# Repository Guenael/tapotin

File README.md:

# tapotin

# Description

Tapotin is a simple 42-keys ortho-linear keyboard, based on QMK driver and a Raspberry Pico (RP2040). The design is heavily inspired by the community, specially by [Pi5Keyboard](https://github.com/luke-schutt/Pi5Keyboard) and [chocV](https://github.com/brickbots/chocV) projects.

Kicad was used for the PCB design, and it was a nice project to switch from professional tools to a community/free PCB editor. For this first version, I used a RPi Pico board, but I plan to solder the RP2040 directly on the main PCB if I like this new keyboard.

# My requirements

- [QMK](https://qmk.fm/) based
- [RP2040](https://en.wikipedia.org/wiki/RP2040) based
- Mono-block (non-split keyboard, I tried it, and I don't like it)
- [Ortholinear](https://en.wiktionary.org/wiki/ortholinear) (offset only for the pinky)
- Left/right clear separation
- Angle 2x 10°
- 42 keys: 2*((3*6)+3)
- [Miryoku](https://github.com/manna-harbour/miryoku) layout based
- PCB specs:
  - Base/solder : 1.6mm
  - Keys plate  : 1.2mm

# Assembly

The RPi Pico board is soldered up-side down, and touch both PCB (main & key plate)

PCB layers overviews:

Back of the keyboard:

# My layout 

Here there be dragons... 20 years ago, I designed my own version of a [Dvorak layout](https://en.wikipedia.org/wiki/Dvorak_keyboard_layout), that include some requirements around programming, and accents. I like it, and I have to go all in one more time, because after 20 years, there is no way back :)

I really liked the concept of [Miryoku](https://github.com/manna-harbour/miryoku) keyboard, so I created my own version based on my custom Dvorak. One of the main difference with the original Miryoku design is that I keep an extra column for the pinky, for 3D/CAD applications with a direct access to some meta keys.

Note: Do not follow my layout, it's very specific, but if your are curious, you can check this page full of references and ideas: [Best layouts](https://www.keyboard-design.com/best-layouts.html) 

# QMK section

## Bootloader

Enter the bootloader mode by holding the RP2040 reset button down while plugging it in.

## Build and flash (using the container method)

1. Clone this repository:

```bash
git clone https://github.com/Guenael/tapotin
cd tapotin
git submodule update --init --recursive
cd qmk_firmware
```
2. Edit your mapping if required (e.g. `keyboards/tapotin/keymaps/default/keymap.c`)

`vi keyboards/tapotin/keymaps/default/keymap.c`

3. Build the firmware using Podman:
```bash
podman run -it --rm --volume "$(pwd):/qmk_userspace" ghcr.io/qmk/qmk_cli:latest bash
```

And once in the container:
```bash
cd /qmk_userspace
make tapotin:default
# make tapotin:dvorak_custom_hw
```

4. Flash the Raspberry Pico:

Put the Raspberry Pico in DFU mode: Enter the bootloader mode by holding the RP2040 reset button down while plugging it in.
(or use the keybord shortcut -- only works if you already use this Keyboard) 

Drag an drop the file on `uf2` file on the USB device. That's it!

## Alternate method

Use the installer script here: https://install.qmk.fm

## Documentation

- [Build environment setup](https://docs.qmk.fm/#/getting_started_build_tools)
- [Make instructions](https://docs.qmk.fm/#/getting_started_make_guide)
- [QMK Guide](https://docs.qmk.fm/#/newbs)

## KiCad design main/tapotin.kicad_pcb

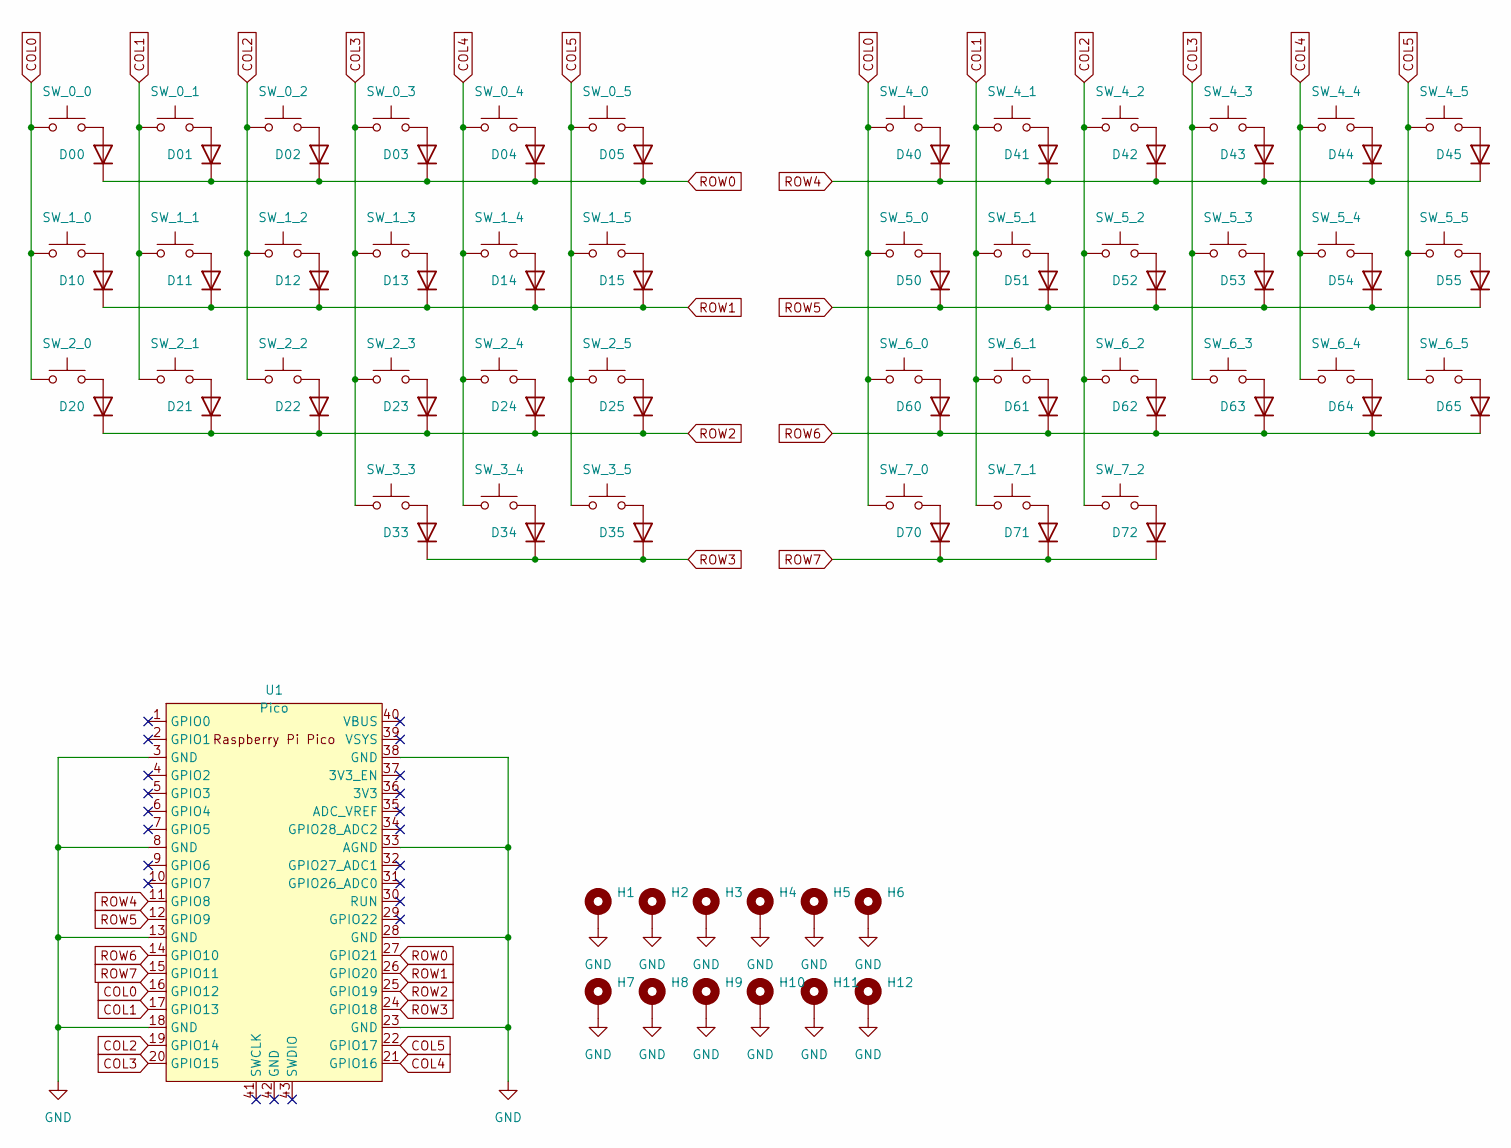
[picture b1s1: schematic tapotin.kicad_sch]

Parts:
D00, D01, D02, D03, D04, D05, D10, D11, D12, D13, D14, D15, D20, D21, D22, D23, D24, D25, D33, D34, D35, D40, D41, D42, D43, D44, D45, D50, D51, D52, D53, D54, D55, D60, D61, D62, D63, D64, D65, D70, D71, D72: D; my-SOD-123
H1, H2, H3, H4, H5, H6, H7, H8, H9, H10, H11, H12: MountingHole_Pad; MountingHole_2.2mm_M2_Pad_Via
SW_0_0, SW_0_1, SW_0_2, SW_0_3, SW_0_4, SW_0_5, SW_1_0, SW_1_1, SW_1_2, SW_1_3, SW_1_4, SW_1_5, SW_2_0, SW_2_1, SW_2_2, SW_2_3, SW_2_4, SW_2_5, SW_3_3, SW_3_4, SW_3_5, SW_4_0, SW_4_1, SW_4_2, SW_4_3, SW_4_4, SW_4_5, SW_5_0, SW_5_1, SW_5_2, SW_5_3, SW_5_4, SW_5_5, SW_6_0, SW_6_1, SW_6_2, SW_6_3, SW_6_4, SW_6_5, SW_7_0, SW_7_1, SW_7_2: SW_Push; SW_Multi_Profile
U1: Pico; RPi_Pico_Space

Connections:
COL0: SW_0_0.1, SW_1_0.1, SW_2_0.1, SW_4_0.1, SW_5_0.1, SW_6_0.1, SW_7_0.1, U1.16 (GPIO12)
COL1: SW_0_1.1, SW_1_1.1, SW_2_1.1, SW_4_1.1, SW_5_1.1, SW_6_1.1, SW_7_1.1, U1.17 (GPIO13)
COL2: SW_0_2.1, SW_1_2.1, SW_2_2.1, SW_4_2.1, SW_5_2.1, SW_6_2.1, SW_7_2.1, U1.19 (GPIO14)
COL3: SW_0_3.1, SW_1_3.1, SW_2_3.1, SW_3_3.1, SW_4_3.1, SW_5_3.1, SW_6_3.1, U1.20 (GPIO15)
COL4: SW_0_4.1, SW_1_4.1, SW_2_4.1, SW_3_4.1, SW_4_4.1, SW_5_4.1, SW_6_4.1, U1.21 (GPIO16)
COL5: SW_0_5.1, SW_1_5.1, SW_2_5.1, SW_3_5.1, SW_4_5.1, SW_5_5.1, SW_6_5.1, U1.22 (GPIO17)
GND: H1.1, H2.1, H3.1, H4.1, H5.1, H6.1, H7.1, H8.1, H9.1, H10.1, H11.1, H12.1, U1.3 (GND), U1.8 (GND), U1.13 (GND), U1.18 (GND), U1.23 (GND), U1.28 (GND), U1.33 (AGND), U1.38 (GND)
unnamed: D00.2 (A), SW_0_0.2
unnamed: D01.2 (A), SW_0_1.2
unnamed: D02.2 (A), SW_0_2.2
unnamed: D03.2 (A), SW_0_3.2
unnamed: D04.2 (A), SW_0_4.2
unnamed: D05.2 (A), SW_0_5.2
unnamed: D10.2 (A), SW_1_0.2
unnamed: D11.2 (A), SW_1_1.2
unnamed: D12.2 (A), SW_1_2.2
unnamed: D13.2 (A), SW_1_3.2
unnamed: D14.2 (A), SW_1_4.2
unnamed: D15.2 (A), SW_1_5.2
unnamed: D20.2 (A), SW_2_0.2
unnamed: D21.2 (A), SW_2_1.2
unnamed: D22.2 (A), SW_2_2.2
unnamed: D23.2 (A), SW_2_3.2
unnamed: D24.2 (A), SW_2_4.2
unnamed: D25.2 (A), SW_2_5.2
unnamed: D33.2 (A), SW_3_3.2
unnamed: D34.2 (A), SW_3_4.2
unnamed: D35.2 (A), SW_3_5.2
unnamed: D40.2 (A), SW_4_0.2
unnamed: D41.2 (A), SW_4_1.2
unnamed: D42.2 (A), SW_4_2.2
unnamed: D43.2 (A), SW_4_3.2
unnamed: D44.2 (A), SW_4_4.2
unnamed: D45.2 (A), SW_4_5.2
unnamed: D50.2 (A), SW_5_0.2
unnamed: D51.2 (A), SW_5_1.2
unnamed: D52.2 (A), SW_5_2.2
unnamed: D53.2 (A), SW_5_3.2
unnamed: D54.2 (A), SW_5_4.2
unnamed: D55.2 (A), SW_5_5.2
unnamed: D60.2 (A), SW_6_0.2
unnamed: D61.2 (A), SW_6_1.2
unnamed: D62.2 (A), SW_6_2.2
unnamed: D63.2 (A), SW_6_3.2
unnamed: D64.2 (A), SW_6_4.2
unnamed: D65.2 (A), SW_6_5.2
unnamed: D70.2 (A), SW_7_0.2
unnamed: D71.2 (A), SW_7_1.2
unnamed: D72.2 (A), SW_7_2.2
ROW0: D00.1 (K), D01.1 (K), D02.1 (K), D03.1 (K), D04.1 (K), D05.1 (K), U1.27 (GPIO21)
ROW1: D10.1 (K), D11.1 (K), D12.1 (K), D13.1 (K), D14.1 (K), D15.1 (K), U1.26 (GPIO20)
ROW2: D20.1 (K), D21.1 (K), D22.1 (K), D23.1 (K), D24.1 (K), D25.1 (K), U1.25 (GPIO19)
ROW3: D33.1 (K), D34.1 (K), D35.1 (K), U1.24 (GPIO18)
ROW4: D40.1 (K), D41.1 (K), D42.1 (K), D43.1 (K), D44.1 (K), D45.1 (K), U1.11 (GPIO8)
ROW5: D50.1 (K), D51.1 (K), D52.1 (K), D53.1 (K), D54.1 (K), D55.1 (K), U1.12 (GPIO9)
ROW6: D60.1 (K), D61.1 (K), D62.1 (K), D63.1 (K), D64.1 (K), D65.1 (K), U1.14 (GPIO10)
ROW7: D70.1 (K), D71.1 (K), D72.1 (K), U1.15 (GPIO11)

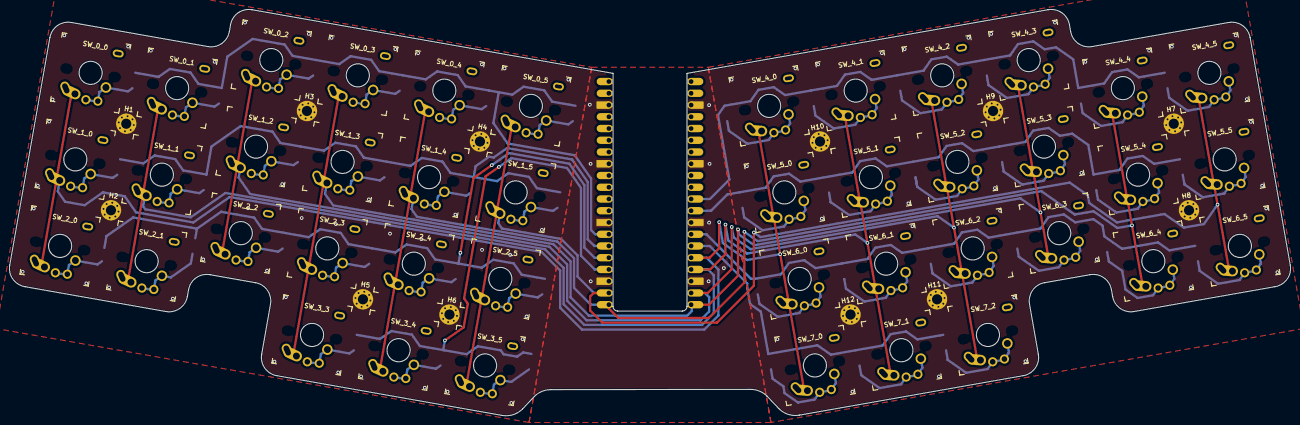
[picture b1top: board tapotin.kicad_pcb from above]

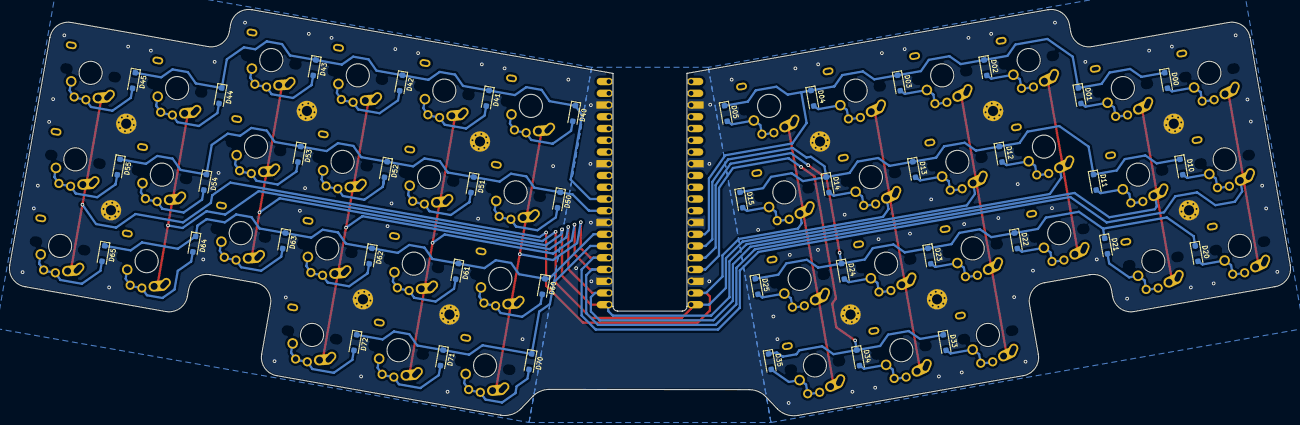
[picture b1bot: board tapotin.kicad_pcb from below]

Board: 2 copper layers, 277.0 x 87.9 mm, 97 parts (43 on the bottom side), 57 nets.

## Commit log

2024-11-25 feat(Projet): Initial Sync.
2024-11-25 fix(readme): Image path fix
2024-12-19 init: Tapotin keyboard rev.A publication
2024-12-19 chore(doc): formatting fix
2026-01-01 chore(mapping): extra key and mouse jiggler update

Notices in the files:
main/tapotin.kicad_pcb:
MIT License
